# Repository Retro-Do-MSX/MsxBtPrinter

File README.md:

# MsxBtPrinter
MSX Bluetooth Printerシールド

## 概要
- ESP-WROOM-32開発ボードを使用したMSX用Bluetoothプリンタインターフェースです。
- MSXのプリンタポートから出力された印刷コマンドを、EPS32とBluetooth接続された三栄電機製モバイルプリンタ`BML-80BT`へ送信、印刷します。
  - MSX
  - -> アンフェノール14ピンケーブル（パラレル）
  - -> ESP-WROOM-32開発ボード＋本シールド
  - -> Bluetooth SPP
  - -> BML-80BT
- ESP-WROOM-32開発ボードには、aitendo「ESP-32でいいの」を使用しています。
- 開発環境はArduino IDEです。
- MSX → ESP32 の端子（D0～D7、~STROBE）は抵抗分圧で 5V → 3.3V にしています。
- ESP32 → MSX の端子（BUSY）は 3.3V のままMSXへ出力します。

## 対応文字
- MSXで使用される ASCII、半角カナ（ANKコード=JIS X 0201）に対応します。
- 2バイト文字（JIS第一水準、JIS第2水準）の漢字は対応しています（つもりです）が、一部の機種依存文字（ローマ数字など）は非対応です。
- グラフィック（ビットイメージ）の印刷は非対応です。
- 半角ひらがなと特殊文字（80H～9FH、E0H～FFH）、グラフィック文字（0140H～015FH）は、`BML-80BT`のダウンロードフォント機能を活用して今後対応予定です。

## 準備
- スケッチ内の変数`slaveAddress`に`BML-80BT`のBluetooth MACアドレス 6バイト を入力しておきます。
- MACアドレスは、`BML-80BT`のユーザーマニュアルに記載の「テスト印字」で確認できます。
  - FEEDボタンを押したまま電源を入れる。
  - STATUS LEDが赤点灯したら、FEEDボタンを離す。
- Arduino IDEでESP-WROOM-32に書き込みます。
- シールドを組み立てます。
  - 回路図内の`Printer IF`コネクタに記載された各ピンの色は、手持ちケーブルのケーブル色（参考）です。
  - 抵抗のワット数は1/4Wでなくても構いません。

## 使い方
- MSXのプリンタポートにケーブルを挿し、MSXと開発ボード、Bluetoothプリンタの電源を入れます。
  - 電源の投入順はどの順番でも構いません。
- 開発ボードとプリンタの接続が完了すると、ビープ音が3回鳴ります。
- MSXで`LPRINT`コマンドなどを打ち込むと、プリンタから印字されます。
- 印字直後は文字がプリンタ内部に隠れているので、シールド上のボタンを押して紙送りを行います。
- 漢字モードで`LPRINT`コマンドを打ち込むと、プリンタから全角文字が印字されます。

## 部品表
  | ボード | 個数 | 備考 |
  | --- | --- | --- |
  | ESP-WROOM-32 | 1 | https://www.aitendo.com/product/15730 |
  | ESP-32でいいの | 1 | https://www.aitendo.com/product/19514 |
  | 1/4W 抵抗 10k | 9 | |
  | 1/4W 抵抗 20k  | 9 | |
  | タクトスイッチ | 1 | https://www.aitendo.com/product/7048 |
  | アンフェノール14ピンケーブル | 1 | オス |

## 回路図

## 基板イメージ

## 製作例

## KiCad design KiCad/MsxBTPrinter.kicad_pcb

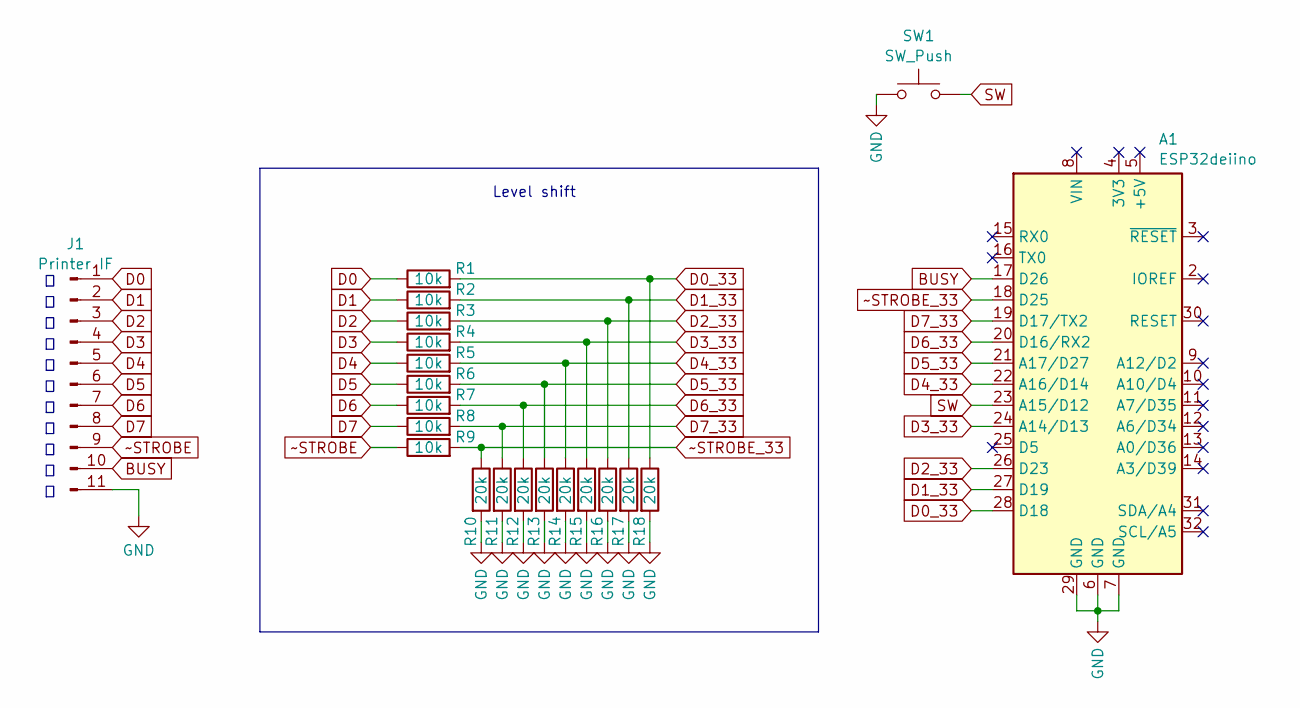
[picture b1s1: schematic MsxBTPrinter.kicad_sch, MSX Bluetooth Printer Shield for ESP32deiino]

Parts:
A1: ESP32deiino; Arduino_UNO_R3
J1: Printer IF; PinHeader_1x11_P2.54mm_Horizontal
R1, R2, R3, R4, R5, R6, R7, R8, R9: 10k; R_Axial_DIN0207_L6.3mm_D2.5mm_P7.62mm_Horizontal
R10, R11, R12, R13, R14, R15, R16, R17, R18: 20k; R_Axial_DIN0204_L3.6mm_D1.6mm_P5.08mm_Horizontal
SW1: SW_Push; SW_PUSH_6mm

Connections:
BUSY: A1.17 (D26), J1.10
D0: J1.1, R1.1
D0_33: A1.28 (D18), R1.2, R18.1
D1: J1.2, R2.1
D1_33: A1.27 (D19), R2.2, R17.1
D2: J1.3, R3.1
D2_33: A1.26 (D23), R3.2, R16.1
D3: J1.4, R4.1
D3_33: A1.24 (A14/D13), R4.2, R15.1
D4: J1.5, R5.1
D4_33: A1.22 (A16/D14), R5.2, R14.1
D5: J1.6, R6.1
D5_33: A1.21 (A17/D27), R6.2, R13.1
D6: J1.7, R7.1
D6_33: A1.20 (D16/RX2), R7.2, R12.1
D7: J1.8, R8.1
D7_33: A1.19 (D17/TX2), R8.2, R11.1
GND: A1.6 (GND), A1.7 (GND), A1.29 (GND), J1.11, R10.2, R11.2, R12.2, R13.2, R14.2, R15.2, R16.2, R17.2, R18.2, SW1.1
SW: A1.23 (A15/D12), SW1.2
~STROBE: J1.9, R9.1
~STROBE_33: A1.18 (D25), R9.2, R10.1

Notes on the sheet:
Level shift

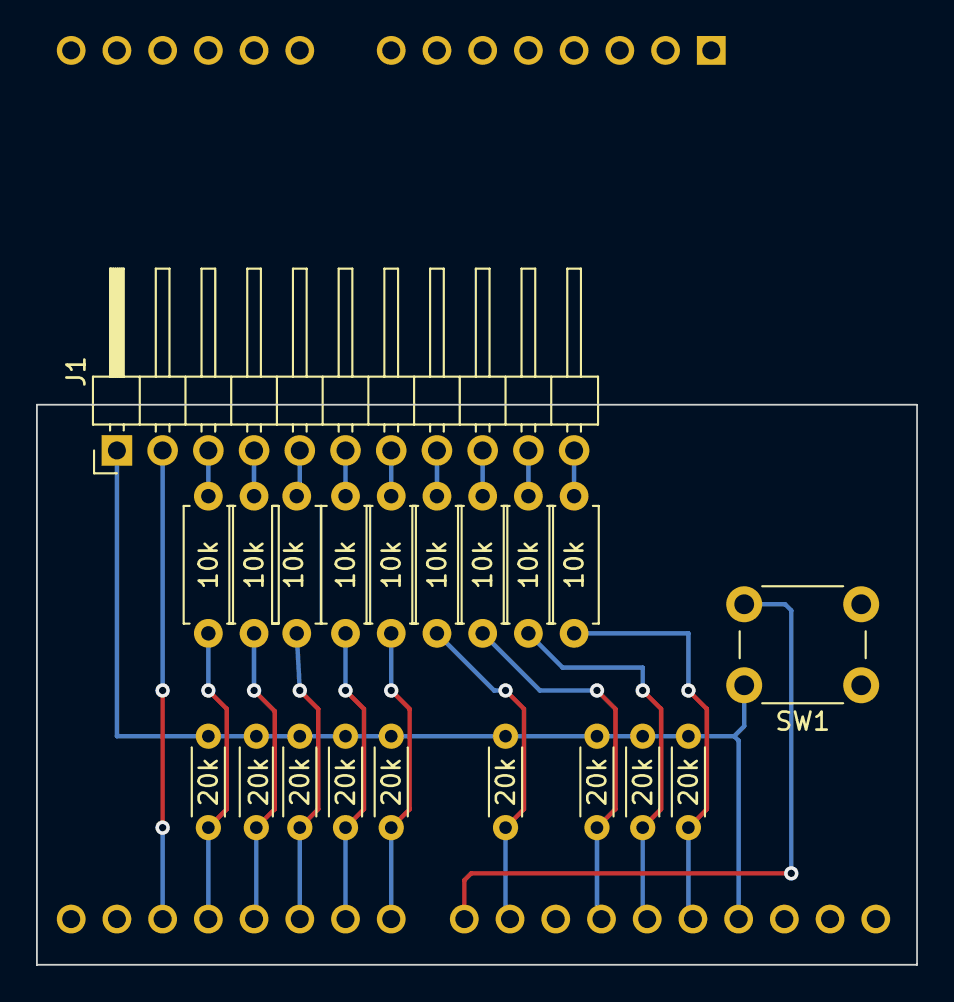
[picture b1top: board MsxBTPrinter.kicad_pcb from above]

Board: 2 copper layers, 48.9 x 31.1 mm, 21 parts (1 on the bottom side), 21 nets.
